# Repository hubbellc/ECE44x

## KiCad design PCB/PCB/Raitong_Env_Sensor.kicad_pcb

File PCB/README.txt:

This folder contains everything utilized in the development of the PCB.
Here you have some basic schematics and images, and then three folders:
	Power holds all the power circuit design
	PCB holds the actual CAD files
		Open using Kicad
	Wiring Design holds the preliminary wiring to get LoRa working

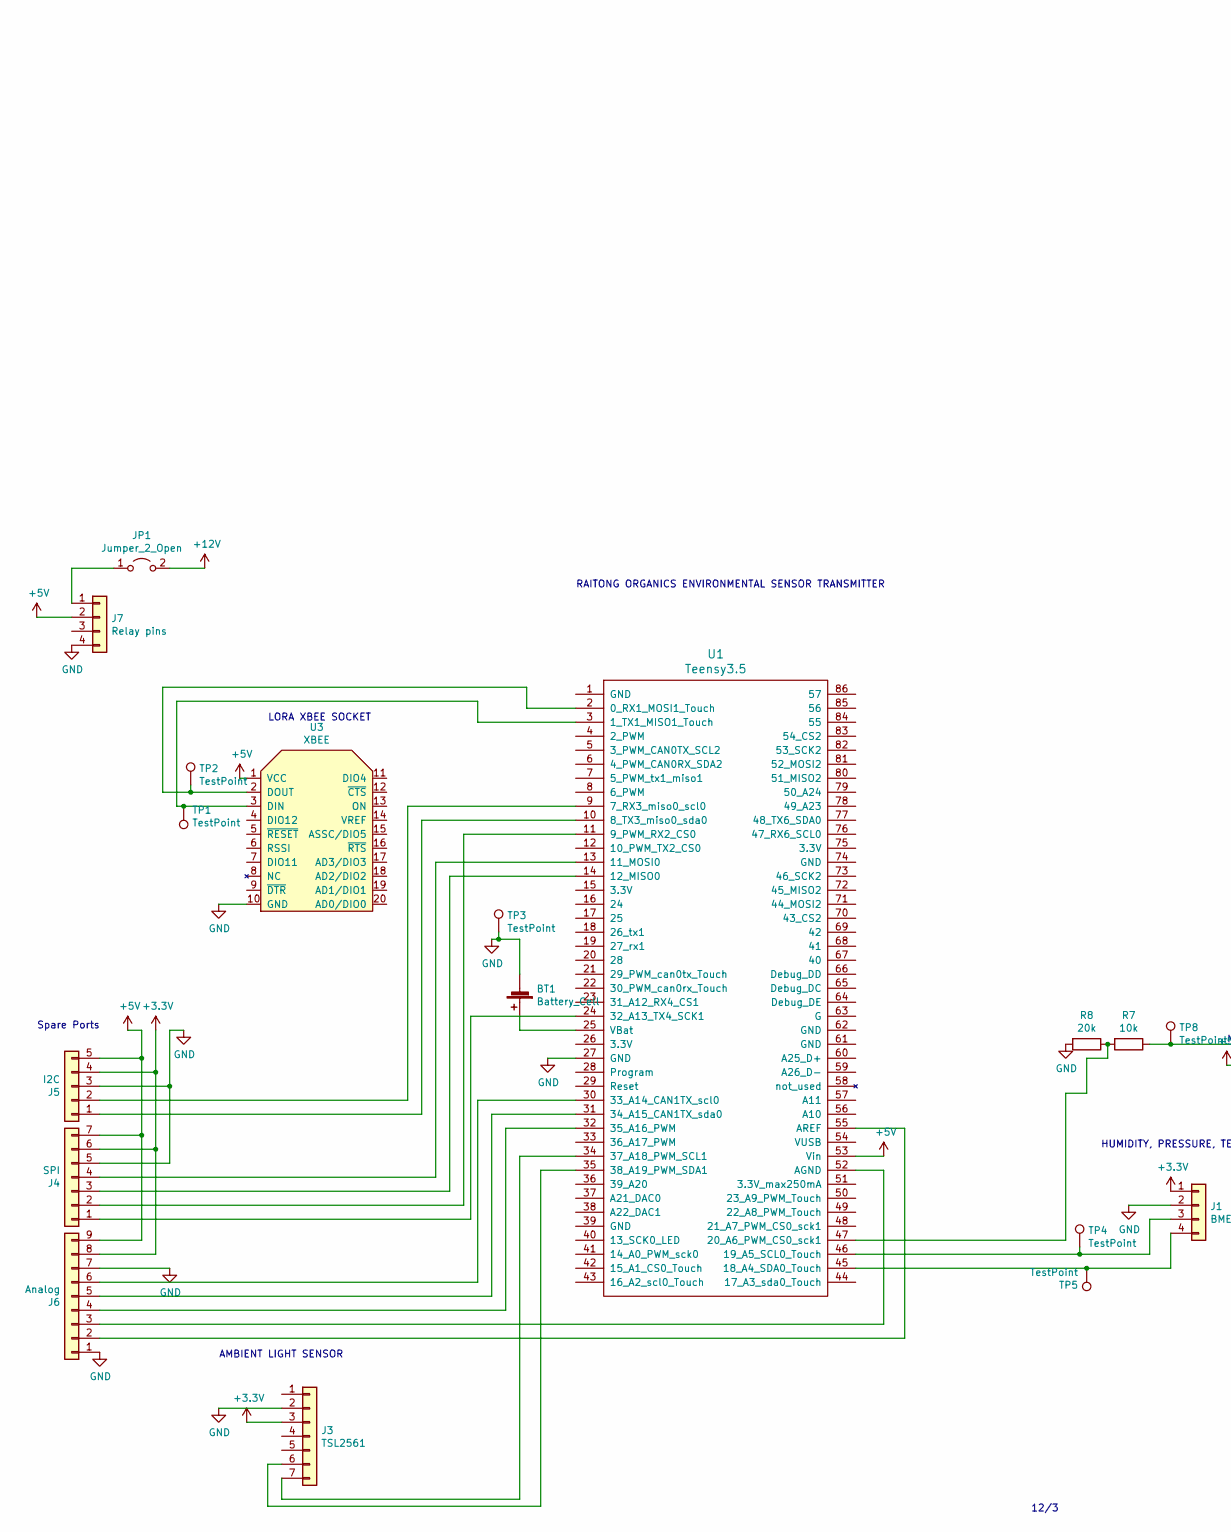
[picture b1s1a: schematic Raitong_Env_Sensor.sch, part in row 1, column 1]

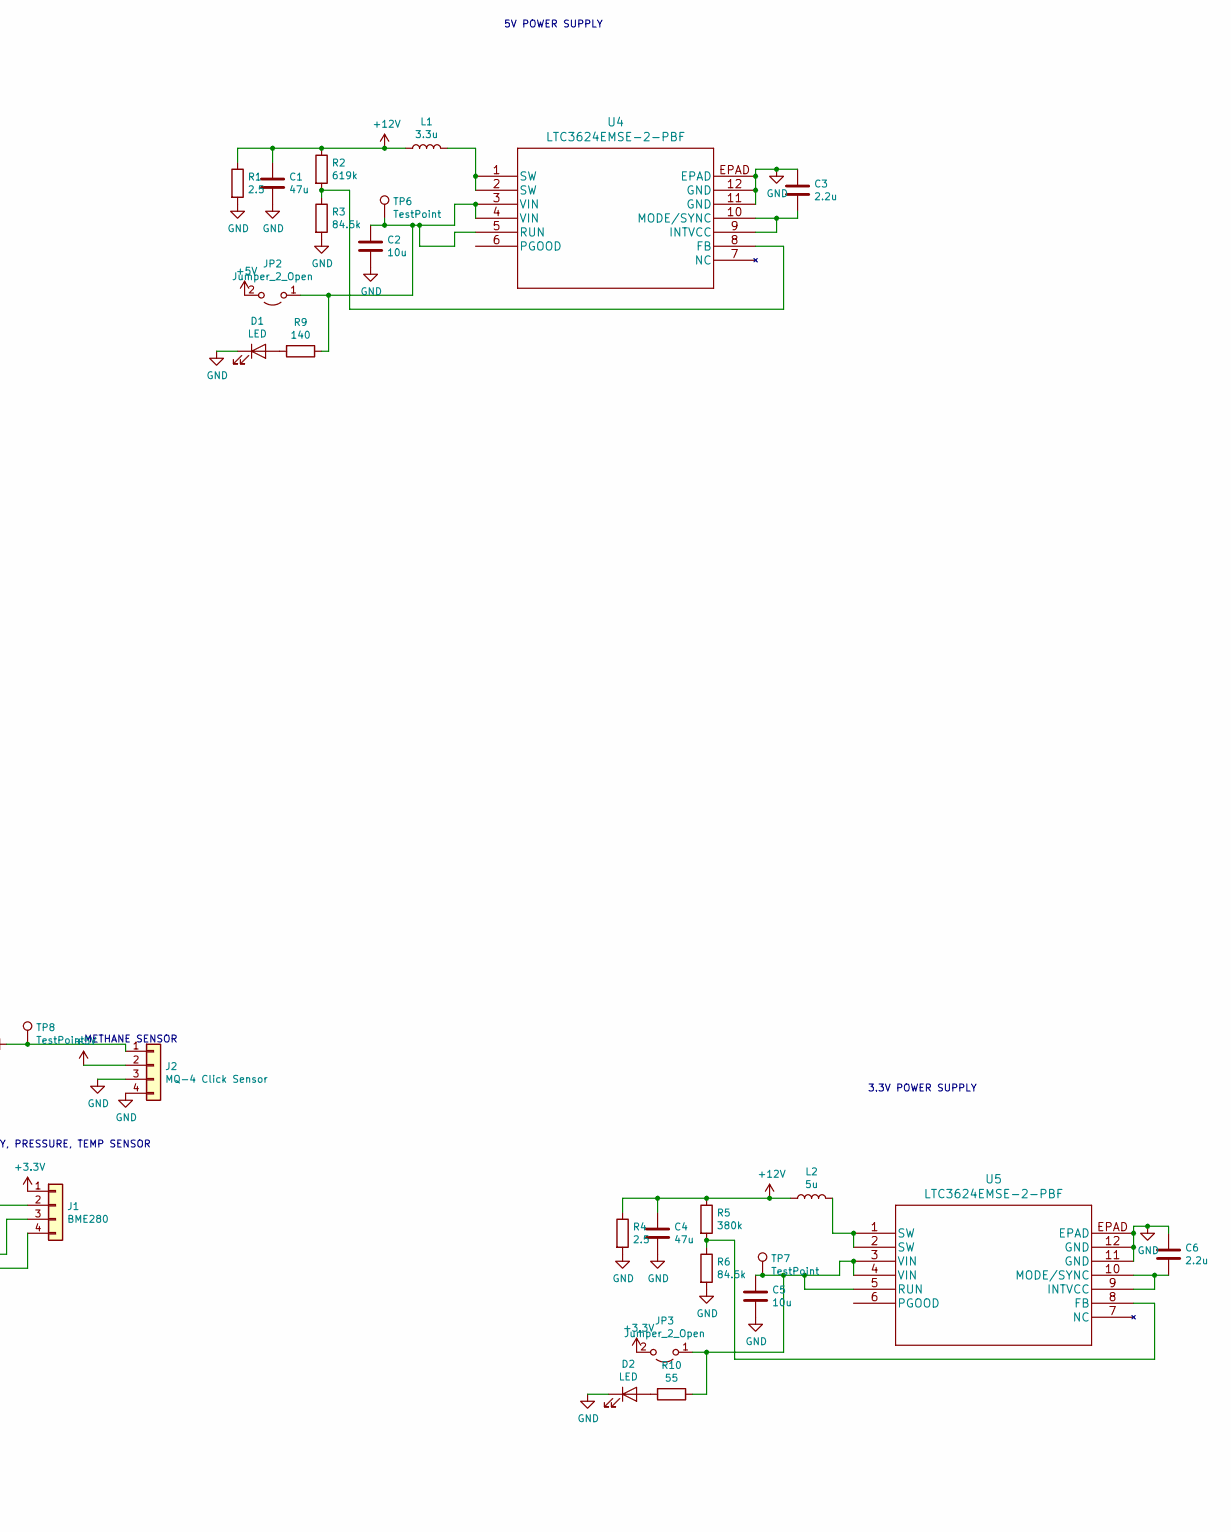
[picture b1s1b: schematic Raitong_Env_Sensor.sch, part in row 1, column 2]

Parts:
BT1: Battery_Cell; BatteryHolder_Keystone_1058_1x2032
C1, C4: 47u; C_0402_1005Metric
C2, C5: 10u; C_0402_1005Metric
C3, C6: 2.2u; C_0402_1005Metric
D1, D2: LED; LED_0603_1608Metric
J1: BME280; PinSocket_1x04_P2.54mm_Vertical_SMD_Pin1Left
J2: MQ-4 Click Sensor; PinSocket_1x04_P2.54mm_Vertical_SMD_Pin1Left
J3: TSL2561; PinSocket_1x07_P2.54mm_Vertical_SMD_Pin1Left
J4: SPI; PinSocket_1x07_P2.54mm_Vertical_SMD_Pin1Left
J5: I2C; PinSocket_1x05_P2.54mm_Vertical_SMD_Pin1Left
J6: Analog; PinSocket_1x09_P2.54mm_Vertical_SMD_Pin1Left
J7: Relay pins; PinSocket_1x04_P2.54mm_Vertical_SMD_Pin1Left
JP1, JP2, JP3: Jumper_2_Open; SolderJumper-2_P1.3mm_Open_Pad1.0x1.5mm
L1: 3.3u; L_0402_1005Metric
L2: 5u; L_0402_1005Metric
R1, R4: 2.5; R_0402_1005Metric
R2: 619k; R_0402_1005Metric
R3, R6: 84.5k; R_0402_1005Metric
R5: 380k; R_0402_1005Metric
R7: 10k; R_0402_1005Metric
R8: 20k; R_0402_1005Metric
R9: 140; R_0402_1005Metric
R10: 55; R_0402_1005Metric
TP1, TP2, TP3, TP4, TP5, TP6, TP7, TP8: TestPoint; TestPoint_Pad_D1.5mm
U1: Teensy3.5; Teensy35_36
U3: XBEE; Xbee_Header_SMD
U4, U5: LTC3624EMSE-2-PBF

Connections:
+3V3: J1.1, J3.3, J4.6, J5.4, J6.8, JP3.2 (B)
+5V: J2.2, J4.7, J5.5, J6.9, J7.2, JP2.2 (B), U1.53 (Vin), U3.1 (VCC)
+12V: C1.1, C4.1, JP1.2 (B), L1.1, L2.1, R1.1, R2.1, R4.1, R5.1
GND: BT1.2 (-), C1.2, C2.2, C3.1, C4.2, C5.2, C6.1, D1.1 (K), D2.1 (K), J1.2, J2.3, J2.4, J3.2, J4.5, J5.3, J6.1, J6.7, J7.4, R1.2, R3.2, R4.2, R6.2, R8.2, TP3.1, U1.27 (GND), U3.10 (GND), U4.11 (GND), U4.12 (GND), U4.EPAD, U5.11 (GND), U5.12 (GND), U5.EPAD
unnamed: BT1.1 (+), U1.25 (VBat)
unnamed: C2.1, JP2.1 (A), R9.1, TP6.1, U4.3 (VIN), U4.4 (VIN), U4.5 (RUN)
unnamed: C3.2, U4.9 (INTVCC), U4.10 (MODE/SYNC)
unnamed: C5.1, JP3.1 (A), R10.1, TP7.1, U5.3 (VIN), U5.4 (VIN), U5.5 (RUN)
unnamed: C6.2, U5.9 (INTVCC), U5.10 (MODE/SYNC)
unnamed: D1.2 (A), R9.2
unnamed: D2.2 (A), R10.2
unnamed: J1.3, TP4.1, U1.46 (19_A5_SCL0_Touch)
unnamed: J1.4, TP5.1, U1.45 (18_A4_SDA0_Touch)
unnamed: J2.1, R7.1, TP8.1
unnamed: J3.6, U1.35 (38_A19_PWM_SDA1)
unnamed: J3.7, U1.34 (37_A18_PWM_SCL1)
unnamed: J4.1, U1.24 (32_A13_TX4_SCK1)
unnamed: J4.2, U1.11 (9_PWM_RX2_CS0)
unnamed: J4.3, U1.14 (12_MISO0)
unnamed: J4.4, U1.13 (11_MOSI0)
unnamed: J5.1, U1.10 (8_TX3_miso0_sda0)
unnamed: J5.2, U1.9 (7_RX3_miso0_scl0)
unnamed: J6.2, U1.55 (AREF)
unnamed: J6.3, U1.52 (AGND)
unnamed: J6.4, U1.32 (35_A16_PWM)
unnamed: J6.5, U1.31 (34_A15_CAN1TX_sda0)
unnamed: J6.6, U1.30 (33_A14_CAN1TX_scl0)
unnamed: J7.1, JP1.1 (A)
unnamed: L1.2, U4.1 (SW), U4.2 (SW)
unnamed: L2.2, U5.1 (SW), U5.2 (SW)
unnamed: R2.2, R3.1, U4.8 (FB)
unnamed: R5.2, R6.1, U5.8 (FB)
unnamed: R7.2, R8.1, U1.47 (20_A6_PWM_CS0_sck1)
unnamed: TP1.1, U1.3 (1_TX1_MISO1_Touch), U3.3 (DIN)
unnamed: TP2.1, U1.2 (0_RX1_MOSI1_Touch), U3.2 (DOUT)

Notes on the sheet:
12/3
HUMIDITY, PRESSURE, TEMP SENSOR
METHANE SENSOR
LORA XBEE SOCKET
AMBIENT LIGHT SENSOR
RAITONG ORGANICS ENVIRONMENTAL SENSOR TRANSMITTER
3.3V POWER SUPPLY
5V POWER SUPPLY
Spare Ports

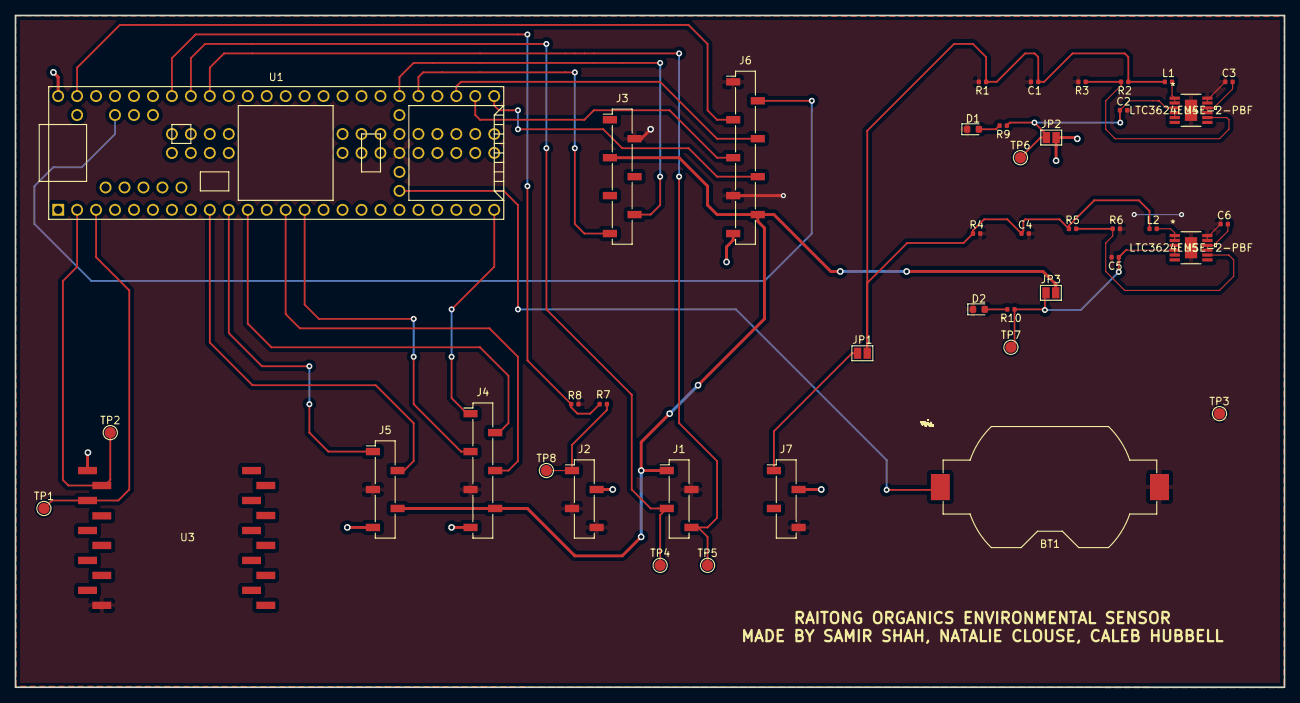
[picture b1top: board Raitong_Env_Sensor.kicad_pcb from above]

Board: 2 copper layers, 170.0 x 90.0 mm, 43 parts (0 on the bottom side), 35 nets.

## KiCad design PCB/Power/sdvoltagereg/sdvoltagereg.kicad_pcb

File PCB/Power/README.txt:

This folder contains all of the power designs.

Progams:
	.asc = LTspice
	
Folder = the kicad design files
	All files in here open in kicad

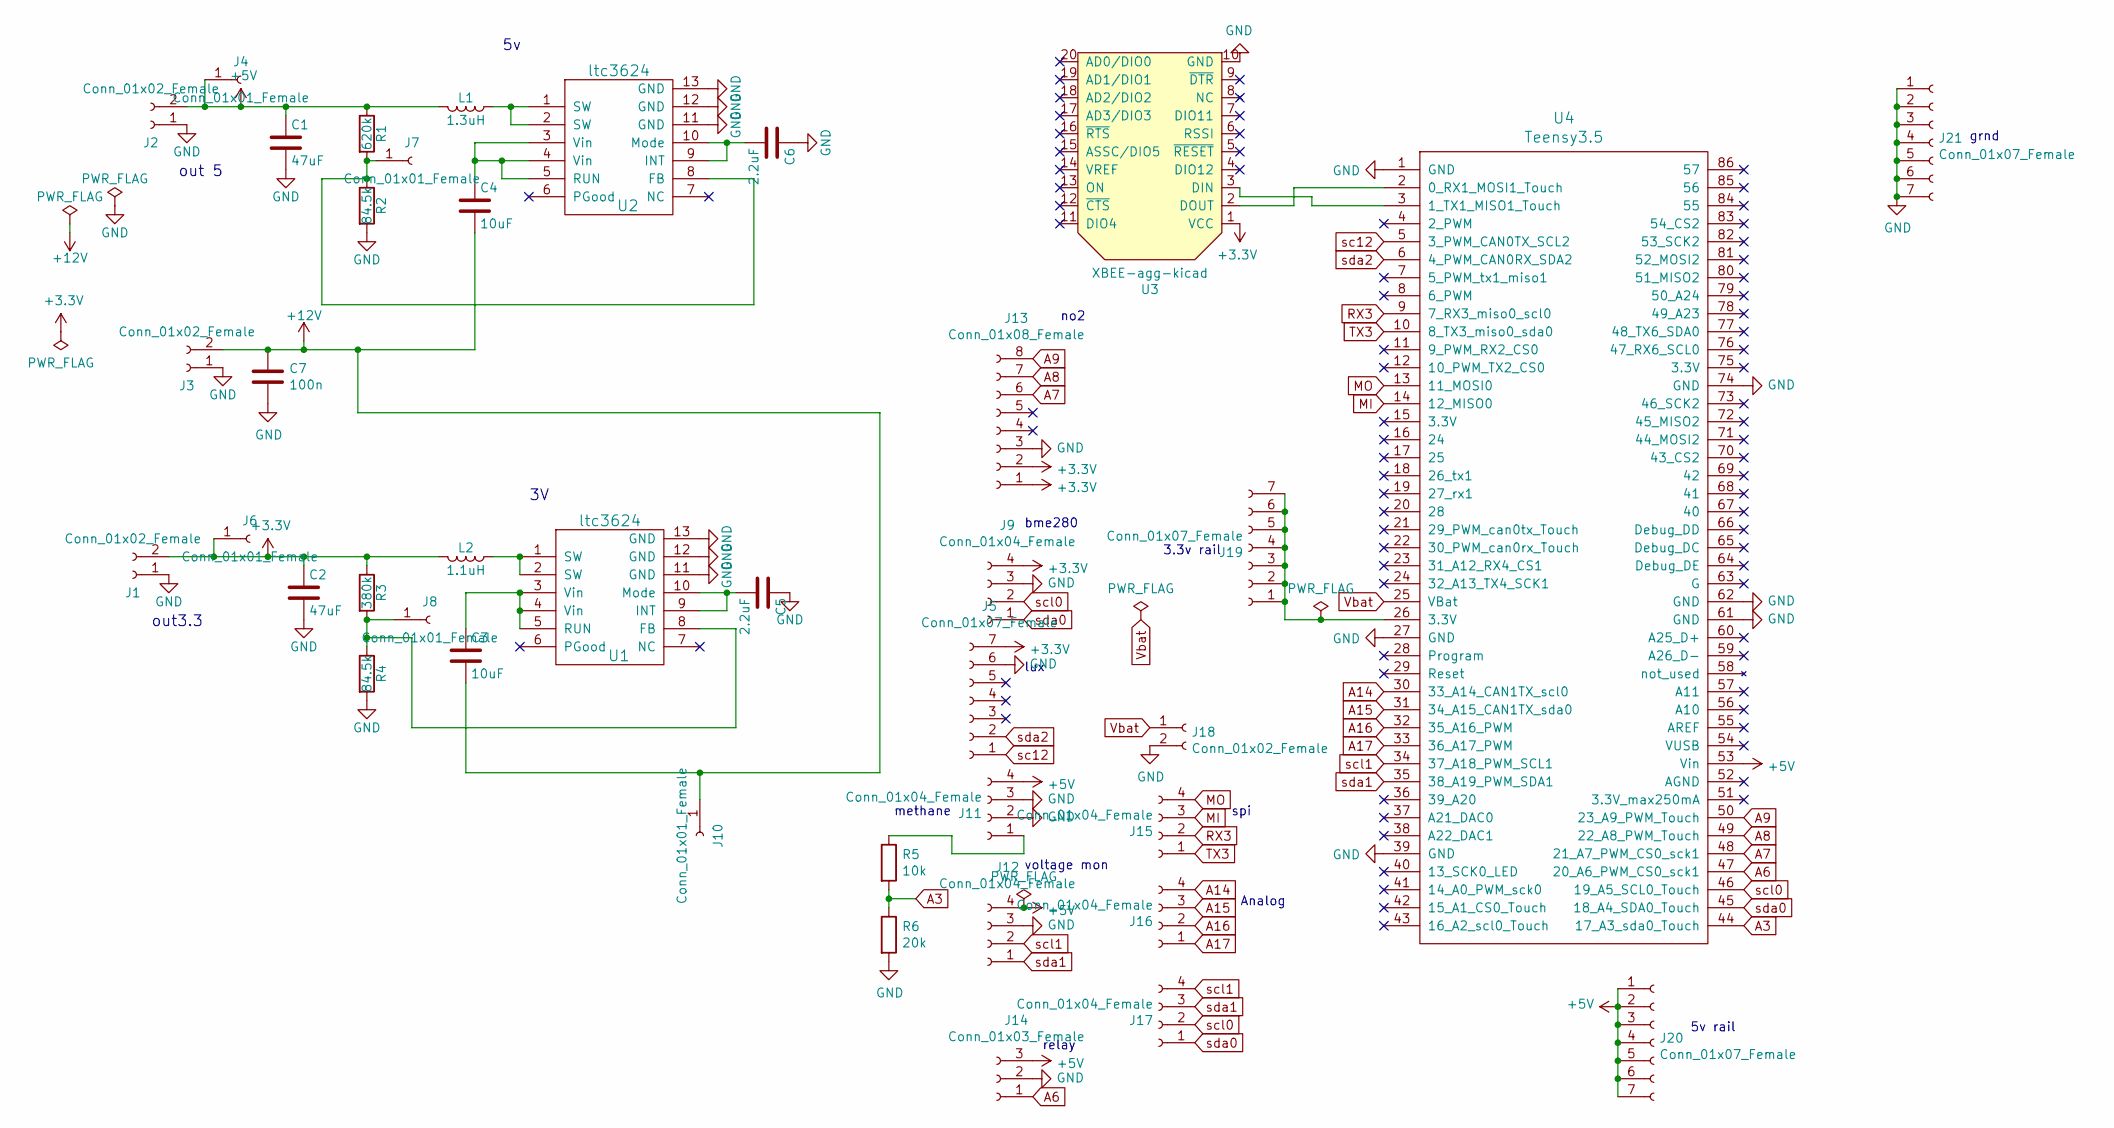
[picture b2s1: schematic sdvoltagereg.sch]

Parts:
C1, C2: 47uF; R_1210_HandSoldering
C3, C4: 10uF; R_0603_HandSoldering
C5, C6: 2.2uF; R_1210_HandSoldering
C7: 100n; C_0603_HandSoldering
J1, J2, J3, J18: Conn_01x02_Female; Pin_Header_Straight_1x02_Pitch2.54mm
J4, J6, J7, J8, J10: Conn_01x01_Female; Pin_Header_Straight_1x01_Pitch2.54mm
J5, J19, J20, J21: Conn_01x07_Female; Pin_Header_Straight_1x07_Pitch2.54mm
J9, J11, J12, J15, J16, J17: Conn_01x04_Female; Pin_Header_Straight_1x04_Pitch2.54mm
J13: Conn_01x08_Female; Pin_Header_Straight_1x08_Pitch2.54mm
J14: Conn_01x03_Female; Pin_Header_Straight_1x03_Pitch2.54mm
L1: 1.3uH; L_0805_HandSoldering
L2: 1.1uH; L_0805_HandSoldering
R1: 620k; R_0603_HandSoldering
R2, R4: 84.5k; R_0402
R3: 380k; R_0603_HandSoldering
R5: 10k; R_0603_HandSoldering
R6: 20k; R_0603_HandSoldering
U1, U2: ltc3624; SOP65P490X110-13N
U3: XBEE-agg-kicad; XBEE
U4: Teensy3.5; Teensy35_36

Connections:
+3V3: C2.1, J1.2, J5.7, J6.1, J9.4, J13.1, J13.2, L2.2, R3.1, U3.1 (VCC)
+5V: C1.1, J2.2, J4.1, J11.4, J12.4, J14.3, J20.1, J20.2, J20.3, J20.4, J20.5, J20.6, J20.7, L1.2, R1.1, U4.53 (Vin)
+12V: C3.2, C4.2, C7.1, J3.2, J10.1
A3: R5.2, R6.1, U4.44 (17_A3_sda0_Touch)
A6: J14.1, U4.47 (20_A6_PWM_CS0_sck1)
A7: J13.6, U4.48 (21_A7_PWM_CS0_sck1)
A8: J13.7, U4.49 (22_A8_PWM_Touch)
A9: J13.8, U4.50 (23_A9_PWM_Touch)
A14: J16.4, U4.30 (33_A14_CAN1TX_scl0)
A15: J16.3, U4.31 (34_A15_CAN1TX_sda0)
A16: J16.2, U4.32 (35_A16_PWM)
A17: J16.1, U4.33 (36_A17_PWM)
GND: C1.2, C2.2, C5.1, C6.1, C7.2, J1.1, J2.1, J3.1, J5.6, J9.3, J11.2, J11.3, J12.3, J13.3, J14.2, J18.2, J21.1, J21.2, J21.3, J21.4, J21.5, J21.6, J21.7, R2.2, R4.2, R6.2, U1.11 (GND), U1.12 (GND), U1.13 (GND), U2.11 (GND), U2.12 (GND), U2.13 (GND), U3.10 (GND), U4.1 (GND), U4.27 (GND), U4.39 (GND), U4.61 (GND), U4.62 (GND), U4.74 (GND)
MI: J15.3, U4.14 (12_MISO0)
MO: J15.4, U4.13 (11_MOSI0)
unnamed: C3.1, U1.3 (Vin), U1.4 (Vin), U1.5 (RUN)
unnamed: C4.1, U2.3 (Vin), U2.4 (Vin), U2.5 (RUN)
unnamed: C5.2, U1.9 (INT), U1.10 (Mode)
unnamed: C6.2, U2.9 (INT), U2.10 (Mode)
unnamed: J7.1, R1.2, R2.1, U2.8 (FB)
unnamed: J8.1, R3.2, R4.1, U1.8 (FB)
unnamed: J11.1, R5.1
unnamed: J19.1, J19.2, J19.3, J19.4, J19.5, J19.6, J19.7, U4.26 (3.3V)
unnamed: L1.1, U2.1 (SW), U2.2 (SW)
unnamed: L2.1, U1.1 (SW), U1.2 (SW)
unnamed: U3.2 (DOUT), U4.2 (0_RX1_MOSI1_Touch)
unnamed: U3.3 (DIN), U4.3 (1_TX1_MISO1_Touch)
RX3: J15.2, U4.9 (7_RX3_miso0_scl0)
TX3: J15.1, U4.10 (8_TX3_miso0_sda0)
Vbat: J18.1, U4.25 (VBat)
sc12: J5.1, U4.5 (3_PWM_CAN0TX_SCL2)
scl0: J9.2, J17.2, U4.46 (19_A5_SCL0_Touch)
scl1: J12.2, J17.4, U4.34 (37_A18_PWM_SCL1)
sda0: J9.1, J17.1, U4.45 (18_A4_SDA0_Touch)
sda1: J12.1, J17.3, U4.35 (38_A19_PWM_SDA1)
sda2: J5.2, U4.6 (4_PWM_CAN0RX_SDA2)

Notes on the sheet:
out 5
out3.3
no2
bme280
lux
voltage mon
methane
5v rail
grnd
3.3v rail
relay
spi
Analog

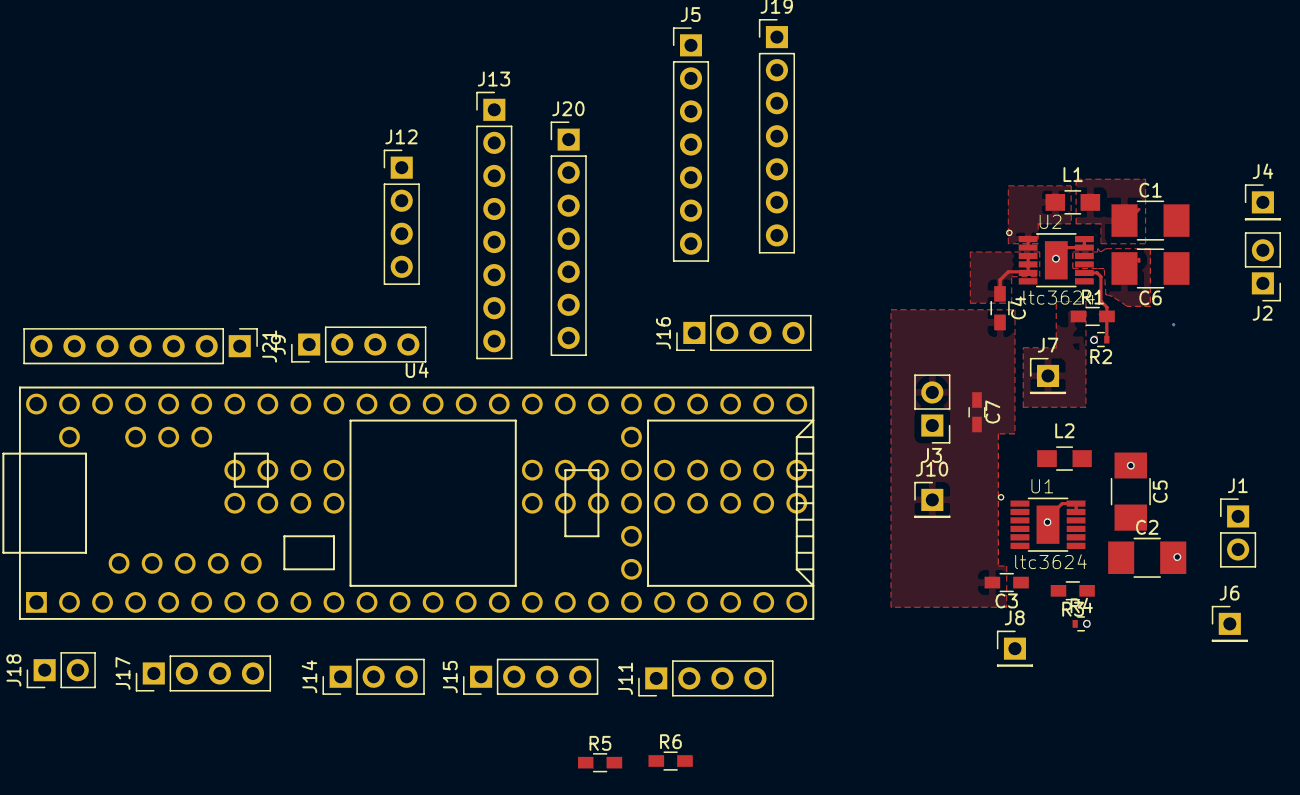
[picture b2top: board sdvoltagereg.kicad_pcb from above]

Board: 2 copper layers, 39 parts (0 on the bottom side), 34 nets.

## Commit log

2019-01-10 First push
2019-01-10 Configured to test Range
2019-01-10 Chaged to test Range
2019-01-11 Added wiring schematics
2019-01-30 Improvements
2019-02-04 Sensor housing designed
2019-02-14 Revised Housing
    STL's have been sent to print. This is the final version.
2019-02-22 Final modifcations before block checkoff
2019-04-10 Sensor housing V2.0
2019-04-10 Natalies code
    This is code for the relay,temp/hum sensor and no2 sensor
2019-04-19 added light sensor
    added light sensor
2019-04-19 Added relay code
2019-04-22 Updated Housing with new PCB design
2019-04-23 light sensor files fixed
2019-04-23 Code cleanup
    Updated wireless protocol to include ACK's. Updated sensor configs to try for 30 seconds.
2019-04-26 updated le code
2019-04-27 Final push Day 1
2019-04-27 asdfv
2019-04-27 Teensy rev
2019-04-27 Merged teensy code
2019-05-01 Updated code
2019-05-03 Code utilized for system checkoff
2019-05-17 ilksjdflkjsadf
2019-05-17 lksajdflkasjdf
2019-05-28 Reorganization
    All files utilized in the design process should now be on github or hackster.
2019-09-14 Raitong improvements
2019-09-14 Improved Lo-Ra workings and added NH3 sensor
2019-09-14 Pi code merge
2019-09-14 new codes
2019-09-14 more better wifi
2019-09-15 new Pi code
2019-09-15 Adding Wills code
2019-09-16 modified wills code to work with new lora module
2019-09-16 fixed lora config
2019-09-17 Playing with LoRa
2019-09-17 Working Teensy Code
2019-09-17 Receiver working
2019-09-17 Will Receiver Working
2019-09-17 Improve drive logic
2019-09-18 Final Teensy code cleanup
2019-09-18 final push of updated sensor data
2019-09-18 final tweaks for receiver
2019-09-18 Improved sensor pi code
2019-11-09 final revisions from Thailand

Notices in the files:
parts and their libraries:
Copyright 2016 Accelerated Designs. All rights reserved.
